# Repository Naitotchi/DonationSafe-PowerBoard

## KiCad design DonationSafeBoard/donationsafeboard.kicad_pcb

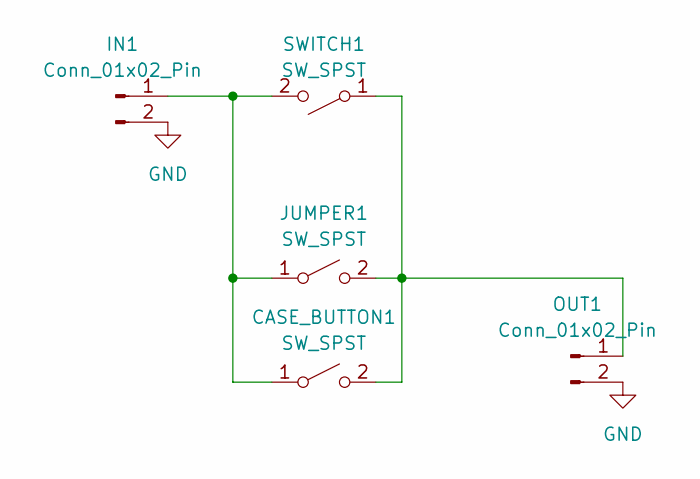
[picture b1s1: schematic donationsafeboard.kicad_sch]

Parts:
CASE_BUTTON1: SW_SPST; JST_XH_B2B-XH-A_1x02_P2.50mm_Vertical
IN1: Conn_01x02_Pin; TerminalBlock_Phoenix_MKDS-1,5-2-5.08_1x02_P5.08mm_Horizont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
JUMPER1: SW_SPST; PinHeader_1x02_P2.54mm_Vertical
OUT1: Conn_01x02_Pin; JST_XH_B2B-XH-A_1x02_P2.50mm_Vertical
SWITCH1: SW_SPST; TerminalBlock_Phoenix_MKDS-1,5-2-5.08_1x02_P5.08mm_Horizont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

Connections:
GND: IN1.2, OUT1.2
unnamed: CASE_BUTTON1.1 (A), IN1.1, JUMPER1.1 (A), SWITCH1.2 (B)
unnamed: CASE_BUTTON1.2 (B), JUMPER1.2 (B), OUT1.1, SWITCH1.1 (A)

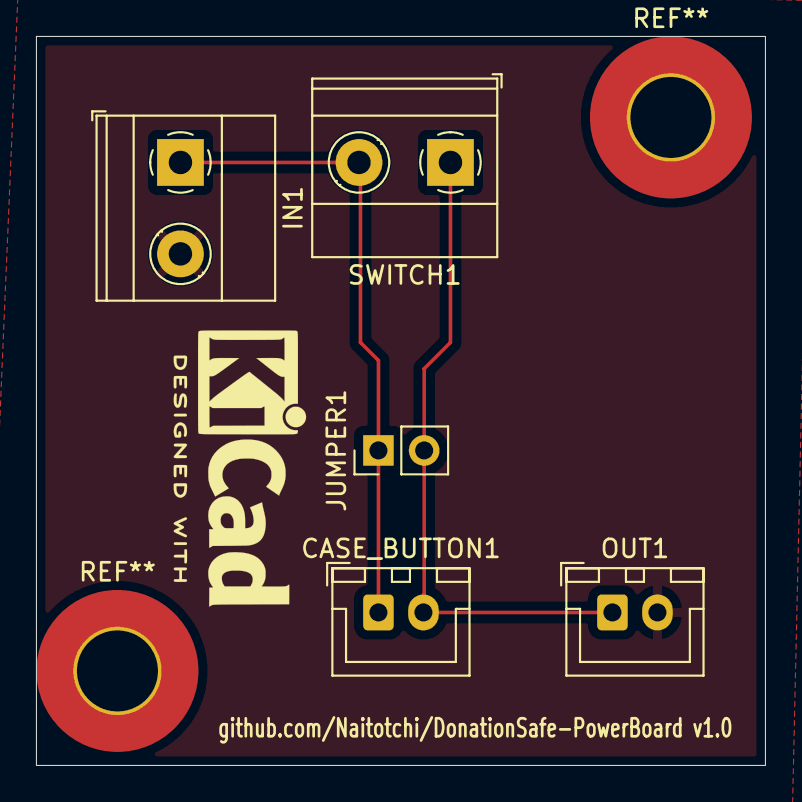
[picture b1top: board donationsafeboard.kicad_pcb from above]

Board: 2 copper layers, 40.5 x 40.5 mm, 5 parts (0 on the bottom side), 3 nets.

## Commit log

2024-12-30 Initial board creation.
    KiCad Board
2024-12-30 put stuff on a board, add holes.
2024-12-30 logos, repo, version.
